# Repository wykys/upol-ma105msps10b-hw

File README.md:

# Multikanálový analyzátor 105 MSPS 10b

Vývoj hardware pro multikanálovou analýzu.

## Datasheets
Technická dokumentace používaná k vývoji.
### FPGA Xilinx 7 Series
- [Vivado Design Suite User Guide](https://www.xilinx.com/support/documentation/sw_manuals/xilinx2016_2/ug908-vivado-programming-debugging.pdf)
- [7 Series FPGAs Data Sheet: Overview](https://www.xilinx.com/support/documentation/data_sheets/ds180_7Series_Overview.pdf)
- [DC and AC Switching Characteristics](https://www.xilinx.com/support/documentation/data_sheets/ds189-spartan-7-data-sheet.pdf)
- [7 Series FPGAs Configuration User Guide](https://www.xilinx.com/support/documentation/user_guides/ug470_7Series_Config.pdf)
- [Using SPI Flash with 7 Series FPGAs](https://www.xilinx.com/support/documentation/application_notes/xapp586-spi-flash.pdf)
- [Spartan-7 FPGA Configuration with SPI Flash and Bank 14 at 1.35V](https://www.xilinx.com/support/documentation/application_notes/xapp1313-spartan-spi-config.pdf)
- [7 Series FPGAs SelectIO Resources User Guide](https://www.xilinx.com/support/documentation/user_guides/ug471_7Series_SelectIO.pdf)
- [7 Series FPGAs PCB Design Guide](https://www.xilinx.com/support/documentation/user_guides/ug483_7Series_PCB.pdf)
- [7 Series FPGAs Packaging and Pinout](https://www.xilinx.com/support/documentation/user_guides/ug475_7Series_Pkg_Pinout.pdf)

### Další dokumenty
- [Přehled logických obvodů ST](https://www.mouser.com/catalog/supplier/library/pdf/STLogic.pdf)
- [Zakončování LVCMOS](https://www.idt.com/eu/en/document/apn/953-quick-guide-output-terminations)
- [USB specifikace](https://www.silabs.com/documents/public/application-notes/AN0046.pdf)

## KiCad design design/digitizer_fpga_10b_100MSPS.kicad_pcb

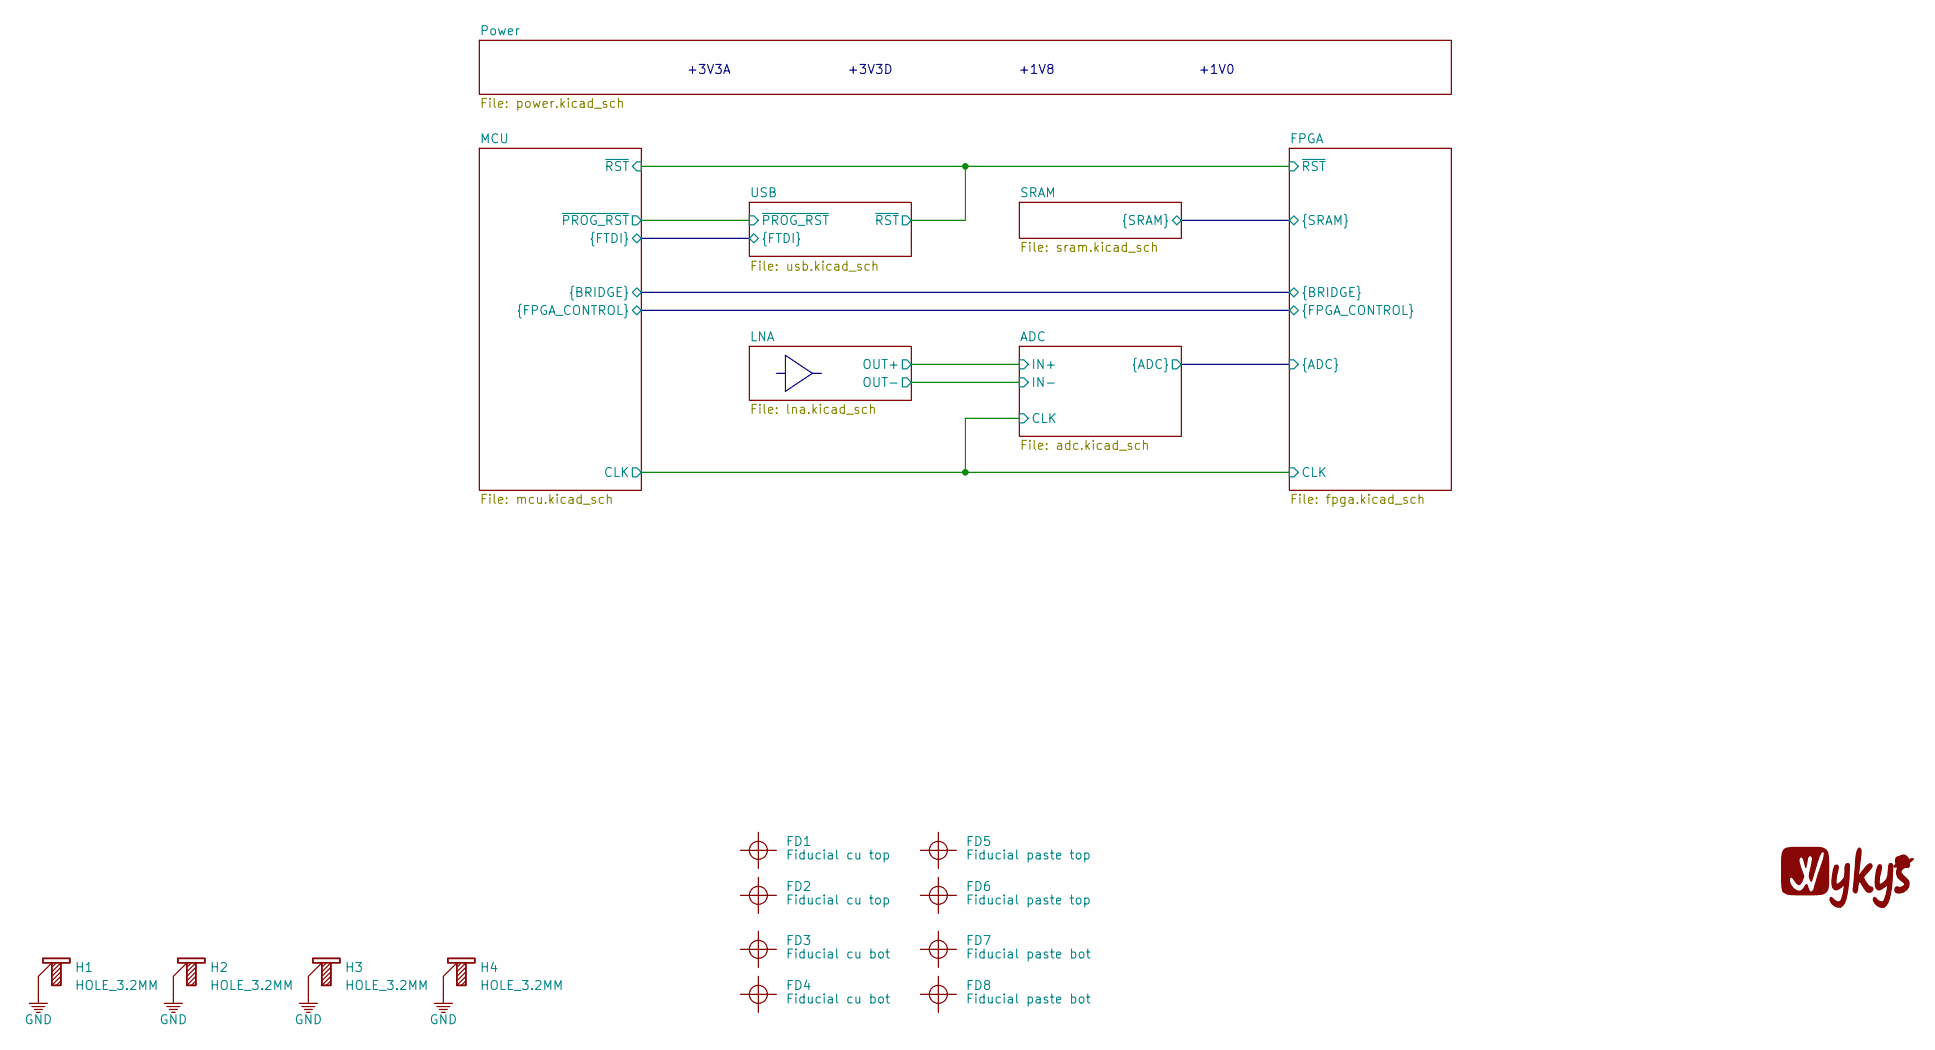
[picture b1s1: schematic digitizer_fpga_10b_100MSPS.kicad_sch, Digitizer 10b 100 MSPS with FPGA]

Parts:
FD1, FD2: Fiducial cu top; Fiducial_Pad_1.5mm_Outer_2.5mm
FD3, FD4: Fiducial cu bot; Fiducial_Pad_1.5mm_Outer_2.5mm
FD5, FD6: Fiducial paste top; Fiducial_Paste_Pad_1.5mm_Outer_2.5mm
FD7, FD8: Fiducial paste bot; Fiducial_Paste_Pad_1.5mm_Outer_2.5mm
GR1: Wykys; wykys_small_skill
H1, H2, H3, H4: HOLE_3.2MM; MountingHole_3.2mm_M3_Pad_Via

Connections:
GND: H1.1, H2.1, H3.1, H4.1; also elsewhere on the board

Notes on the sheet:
+3V3A
+3V3D
+1V8
+1V0

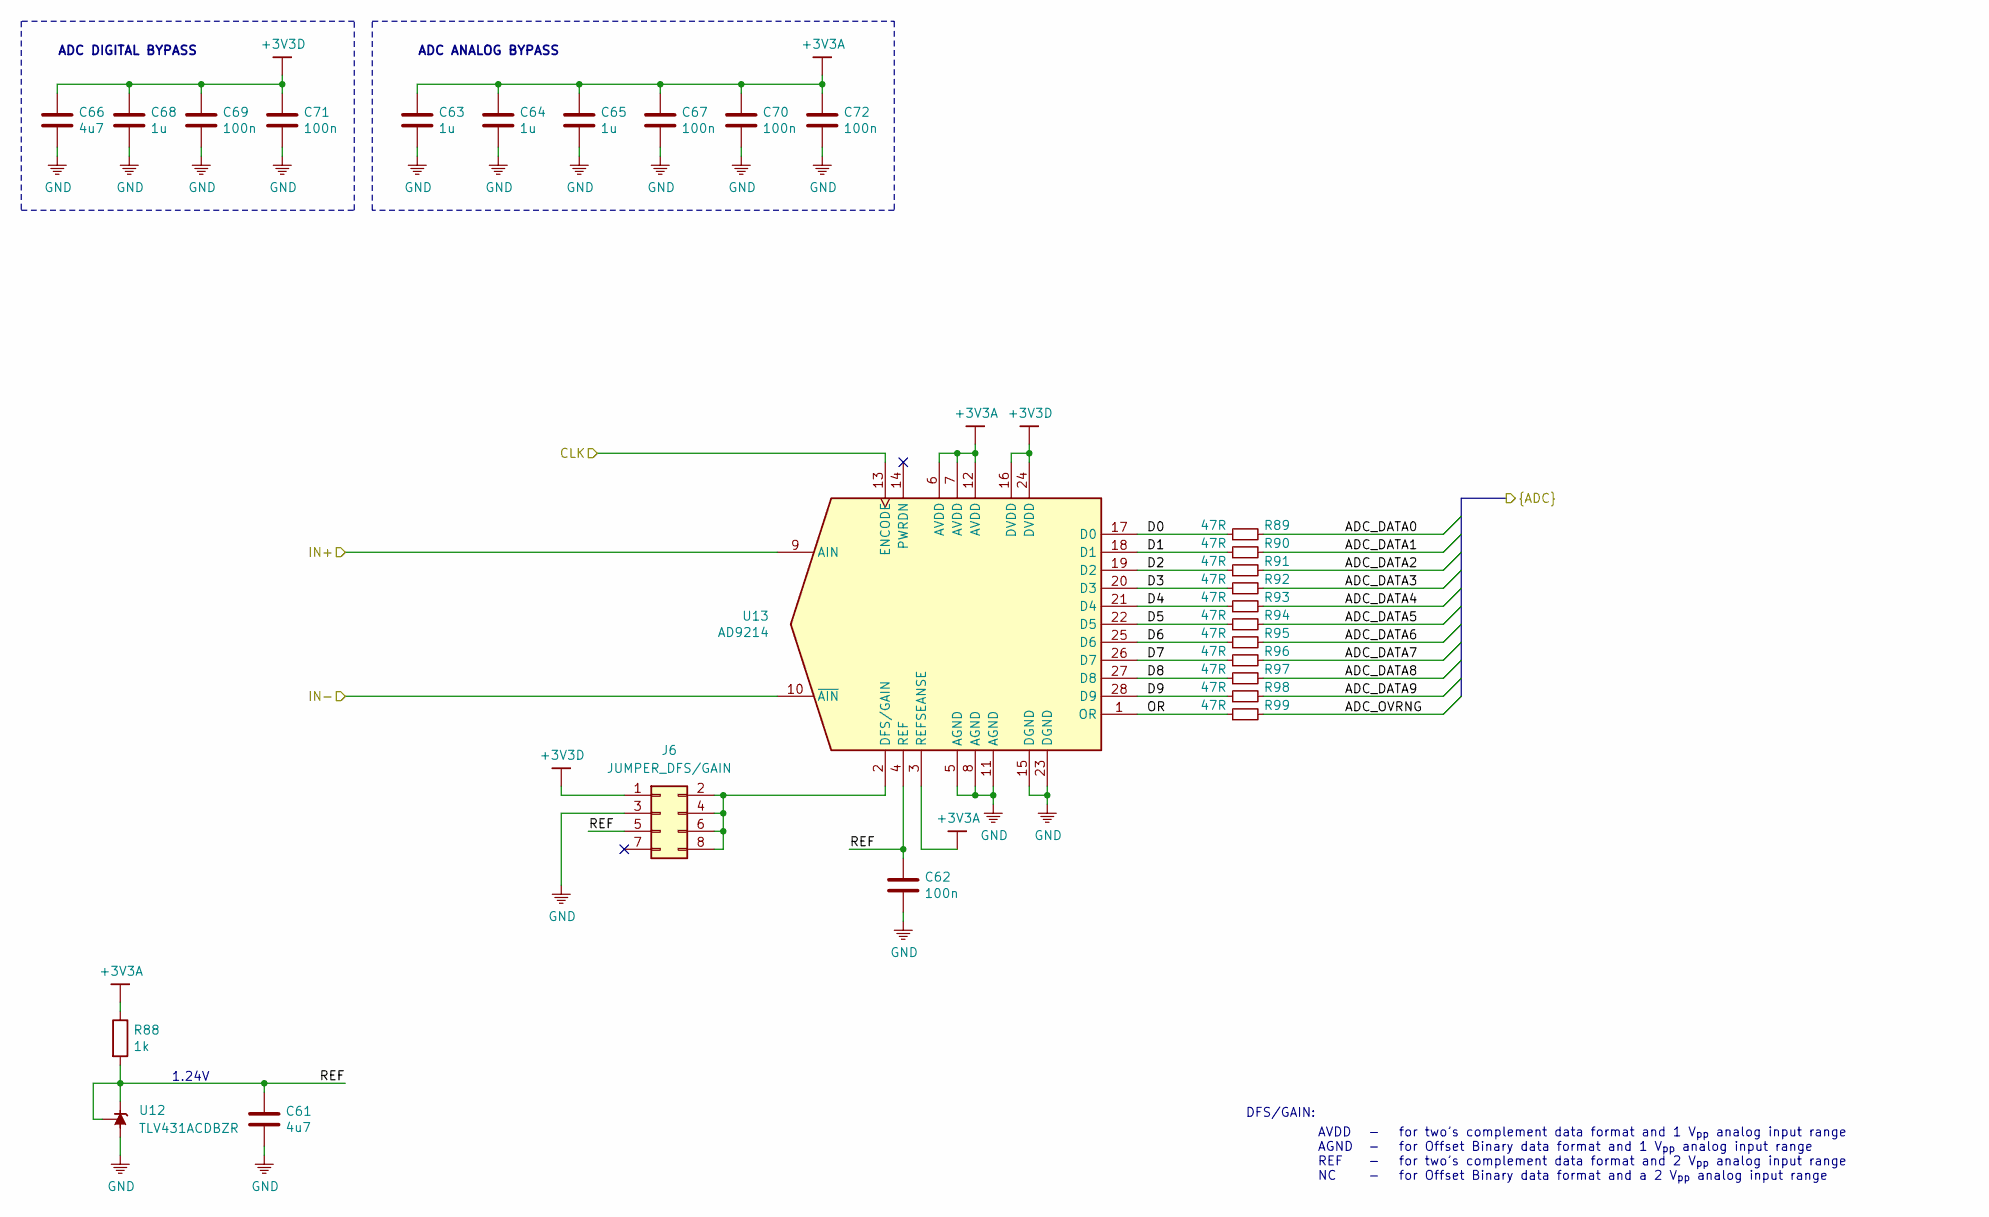
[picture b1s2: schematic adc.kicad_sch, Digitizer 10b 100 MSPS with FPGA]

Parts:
C61, C66: 4u7; C_0402_1005Metric
C62, C67, C69, C70, C71, C72: 100n; C_0402_1005Metric
C63, C64, C65, C68: 1u; C_0402_1005Metric
J6: JUMPER_DFS/GAIN; PinHeader_2x04_P2.54mm_Vertical
R88: 1k; R_0603_1608Metric
R89, R90, R91, R92, R93, R94, R95, R96, R97, R98, R99: 47R; R_0402_1005Metric
U12: TLV431ACDBZR; SOT-23
U13: AD9214; SSOP-28_5.3x10.2mm_P0.65mm

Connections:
+3V3A: C63.1, C64.1, C65.1, C67.1, C70.1, C72.1, R88.1, U13.3 (REFSEANSE), U13.6 (AVDD), U13.7 (AVDD), U13.12 (AVDD); also elsewhere on the board
+3V3D: C66.1, C68.1, C69.1, C71.1, J6.1, U13.16 (DVDD), U13.24 (DVDD); also elsewhere on the board
/ADC/ADC_DATA0: R89.2; also elsewhere on the board
/ADC/ADC_DATA1: R90.2; also elsewhere on the board
/ADC/ADC_DATA2: R91.2; also elsewhere on the board
/ADC/ADC_DATA3: R92.2; also elsewhere on the board
/ADC/ADC_DATA4: R93.2; also elsewhere on the board
/ADC/ADC_DATA5: R94.2; also elsewhere on the board
/ADC/ADC_DATA6: R95.2; also elsewhere on the board
/ADC/ADC_DATA7: R96.2; also elsewhere on the board
/ADC/ADC_DATA8: R97.2; also elsewhere on the board
/ADC/ADC_DATA9: R98.2; also elsewhere on the board
/ADC/ADC_OVRNG: R99.2; also elsewhere on the board
/ADC/CLK: U13.13 (ENCODE); also elsewhere on the board
/ADC/D0: R89.1, U13.17 (D0)
/ADC/D1: R90.1, U13.18 (D1)
/ADC/D2: R91.1, U13.19 (D2)
/ADC/D3: R92.1, U13.20 (D3)
/ADC/D4: R93.1, U13.21 (D4)
/ADC/D5: R94.1, U13.22 (D5)
/ADC/D6: R95.1, U13.25 (D6)
/ADC/D7: R96.1, U13.26 (D7)
/ADC/D8: R97.1, U13.27 (D8)
/ADC/D9: R98.1, U13.28 (D9)
/ADC/IN+: U13.9 (AIN); also elsewhere on the board
/ADC/IN-: U13.10 (~AIN); also elsewhere on the board
/ADC/OR: R99.1, U13.1 (OR)
/ADC/REF: C61.1, C62.1, J6.5, R88.2, U12.1 (K), U12.2 (REF), U13.4 (REF)
GND: C61.2, C62.2, C63.2, C64.2, C65.2, C66.2, C67.2, C68.2, C69.2, C70.2, C71.2, C72.2, J6.3, U12.3 (A), U13.5 (AGND), U13.8 (AGND), U13.11 (AGND), U13.15 (DGND), U13.23 (DGND); also elsewhere on the board
unnamed: J6.2, J6.4, J6.6, J6.8, U13.2 (DFS/GAIN)

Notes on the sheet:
ADC DIGITAL BYPASS
1.24V
ADC ANALOG BYPASS
DFS/GAIN:
AVDD AGND REF NC
- - - -
for two’s complement data format and 1 V_{pp} analog input range for Offset Binary data format and 1 V_{pp} analog input range for two’s complement data format and 2 V_{pp} analog input range for Offset Binary data format and a 2 V_{pp} analog input range

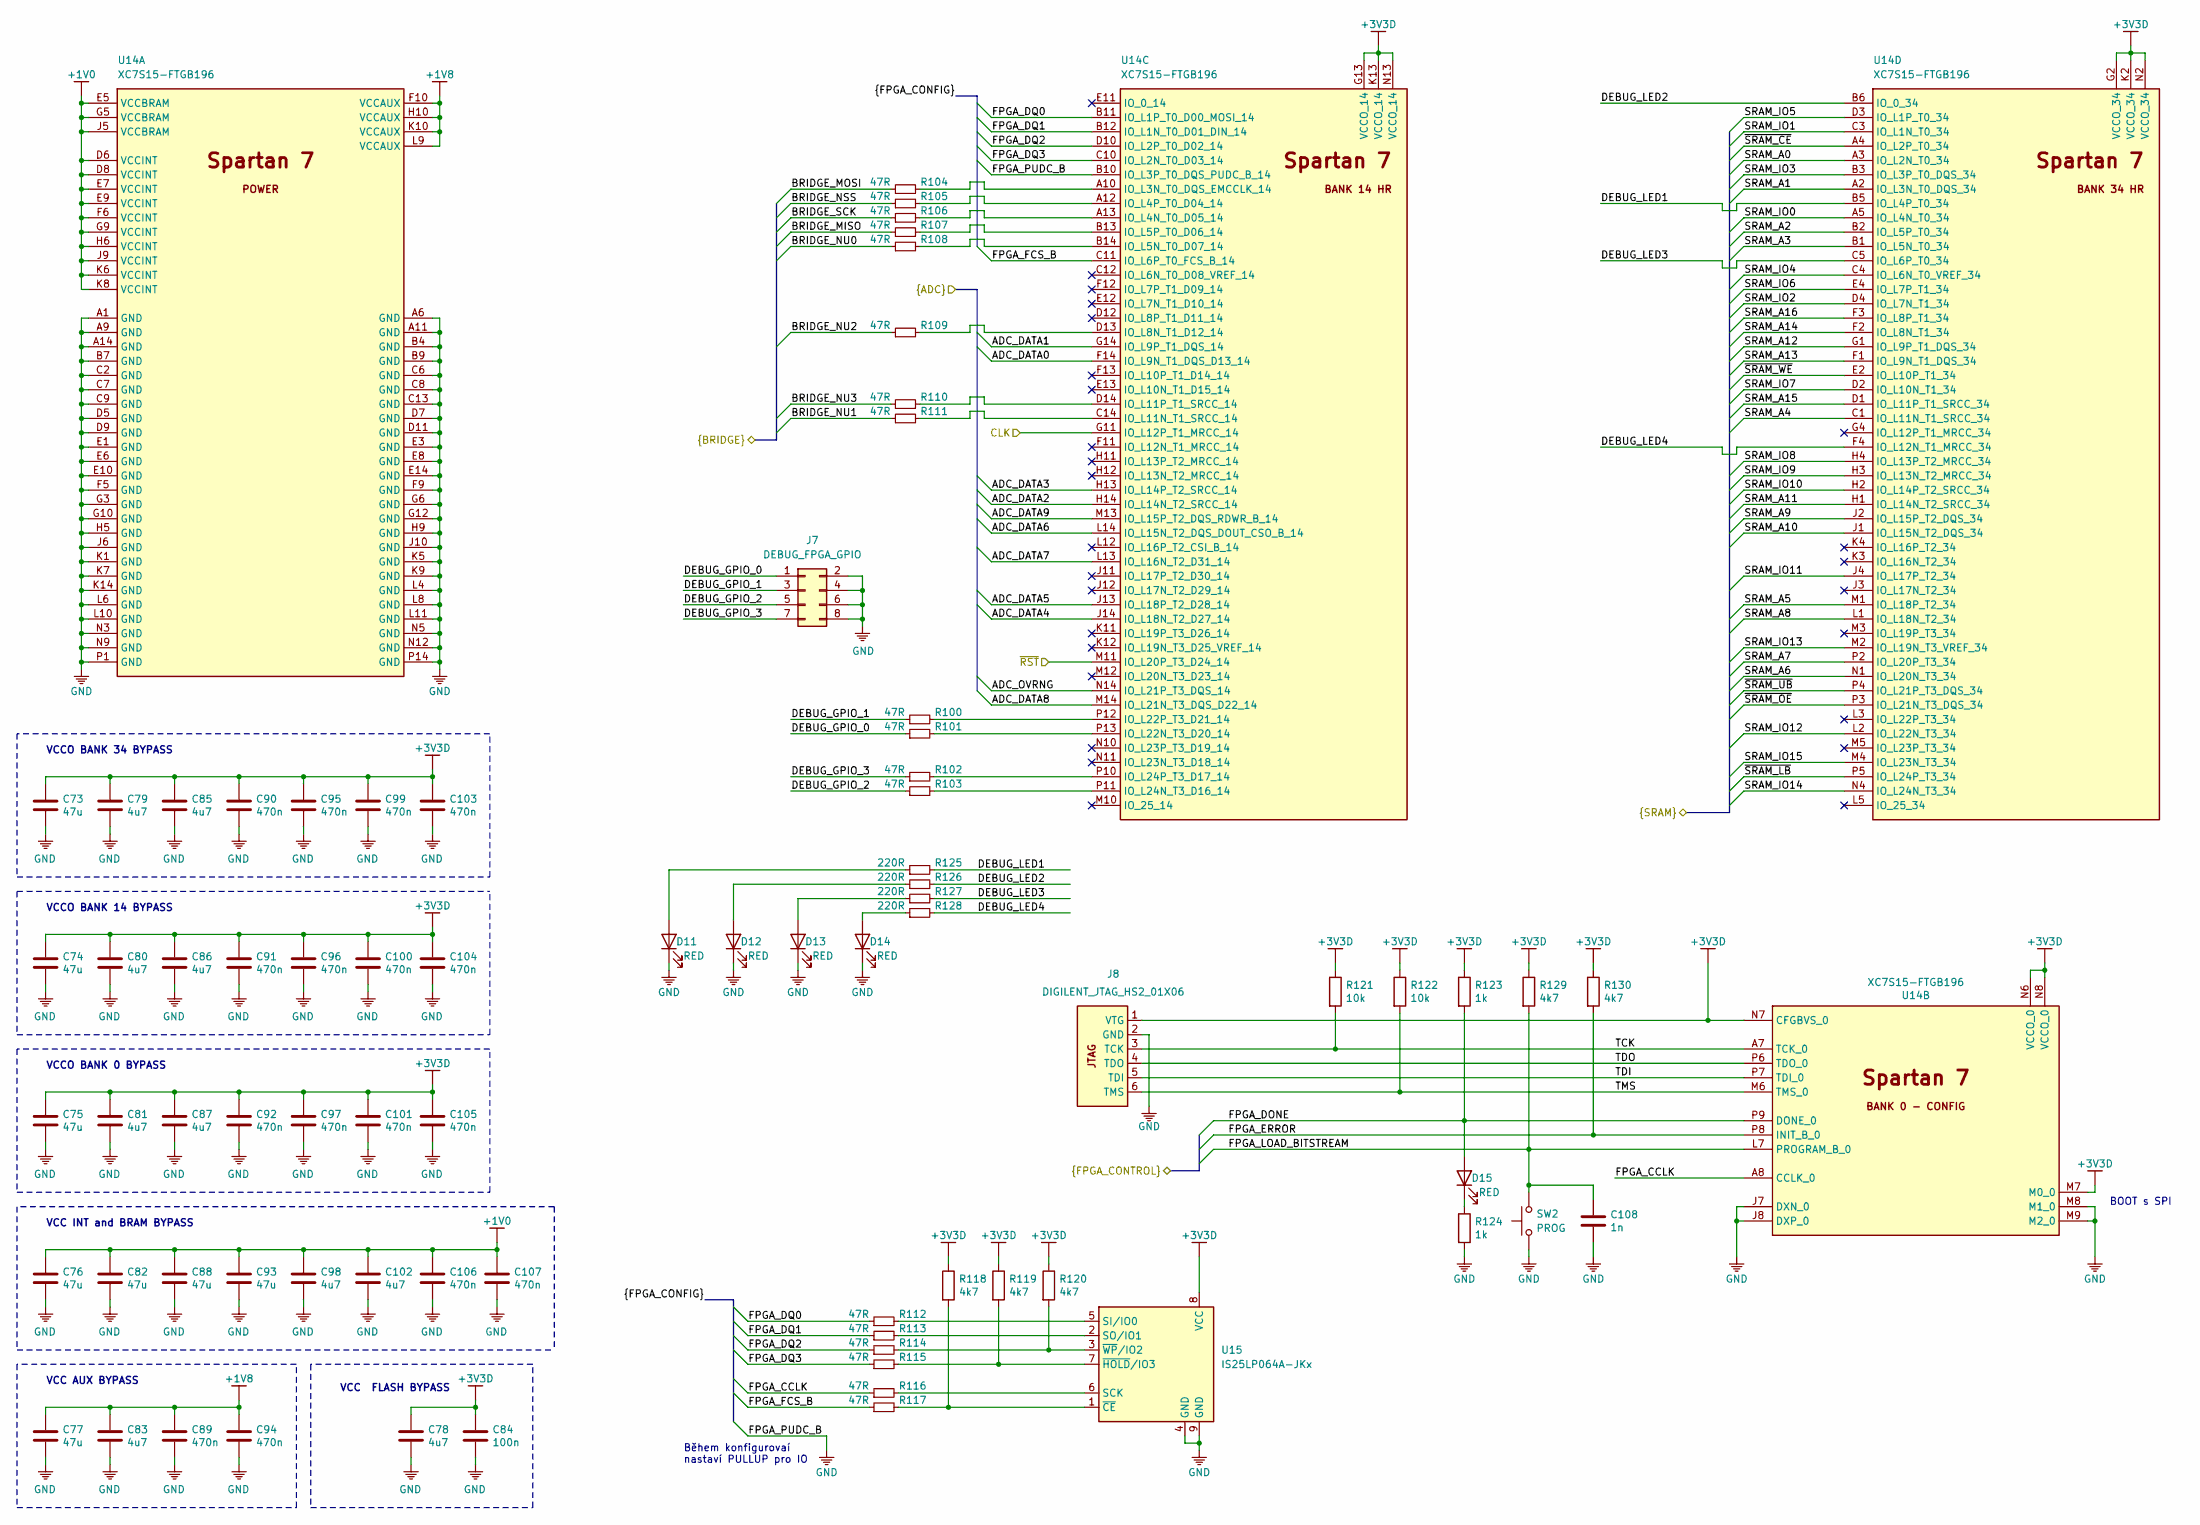
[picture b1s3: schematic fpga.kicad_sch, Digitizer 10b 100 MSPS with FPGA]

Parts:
C73, C74, C75, C76, C77, C82, C88, C93: 47u; C_0402_1005Metric
C78, C79, C80, C81, C83, C85, C86, C87, C98, C102: 4u7; C_0402_1005Metric
C84: 100n; C_0402_1005Metric
C89, C90, C91, C92, C94, C95, C96, C97, C99, C100, C101, C103, C104, C105, C106, C107: 470n; C_0402_1005Metric
C108: 1n; C_0402_1005Metric
D11, D12, D13, D14, D15: RED; LED_0805_2012Metric
J7: DEBUG_FPGA_GPIO; PinHeader_2x04_P2.54mm_Vertical
J8: DIGILENT_JTAG_HS2_01X06; PinHeader_1x06_P2.54mm_Vertical
R100, R101, R102, R103, R104, R105, R106, R107, R108, R109, R110, R111, R112, R113, R114, R115, R116, R117: 47R; R_0402_1005Metric
R118, R119, R120, R129, R130: 4k7; R_0603_1608Metric
R121, R122: 10k; R_0603_1608Metric
R123, R124: 1k; R_0603_1608Metric
R125, R126, R127, R128: 220R; R_0603_1608Metric
SW2: PROG; SW_SPST_CK_RS282G05A3
U14: XC7S15-FTGB196; Xilinx_FTGB196
U15: IS25LP064A-JKx; WSON-8-1EP_6x5mm_P1.27mm_EP3.4x4mm

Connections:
+1V0: C76.1, C82.1, C88.1, C93.1, C98.1, C102.1, C106.1, C107.1, U14.D6 (VCCINT), U14.D8 (VCCINT), U14.E5 (VCCBRAM), U14.E7 (VCCINT), U14.E9 (VCCINT), U14.F6 (VCCINT), U14.G5 (VCCBRAM), U14.G9 (VCCINT), U14.H6 (VCCINT), U14.J5 (VCCBRAM), U14.J9 (VCCINT), U14.K6 (VCCINT), U14.K8 (VCCINT); also elsewhere on the board
+1V8: C77.1, C83.1, C89.1, C94.1, U14.F10 (VCCAUX), U14.H10 (VCCAUX), U14.K10 (VCCAUX), U14.L9 (VCCAUX); also elsewhere on the board
+3V3D: C73.1, C74.1, C75.1, C78.1, C79.1, C80.1, C81.1, C84.1, C85.1, C86.1, C87.1, C90.1, C91.1, C92.1, C95.1, C96.1, C97.1, C99.1, C100.1, C101.1, C103.1, C104.1, C105.1, J8.1 (VTG), R118.1, R119.1, R120.1, R121.1, R122.1, R123.1, R129.1, R130.1, U14.G2 (VCCO_34), U14.G13 (VCCO_14), U14.K2 (VCCO_34), U14.K13 (VCCO_14), U14.M7 (M0_0), U14.N2 (VCCO_34), U14.N6 (VCCO_0), U14.N7 (CFGBVS_0), U14.N8 (VCCO_0), U14.N13 (VCCO_14), U15.8 (VCC); also elsewhere on the board
/ADC/ADC_DATA0: U14.F14 (IO_L9N_T1_DQS_D13_14); also elsewhere on the board
/ADC/ADC_DATA1: U14.G14 (IO_L9P_T1_DQS_14); also elsewhere on the board
/ADC/ADC_DATA2: U14.H14 (IO_L14N_T2_SRCC_14); also elsewhere on the board
/ADC/ADC_DATA3: U14.H13 (IO_L14P_T2_SRCC_14); also elsewhere on the board
/ADC/ADC_DATA4: U14.J14 (IO_L18N_T2_D27_14); also elsewhere on the board
/ADC/ADC_DATA5: U14.J13 (IO_L18P_T2_D28_14); also elsewhere on the board
/ADC/ADC_DATA6: U14.L14 (IO_L15N_T2_DQS_DOUT_CSO_B_14); also elsewhere on the board
/ADC/ADC_DATA7: U14.L13 (IO_L16N_T2_D31_14); also elsewhere on the board
/ADC/ADC_DATA8: U14.M14 (IO_L21N_T3_DQS_D22_14); also elsewhere on the board
/ADC/ADC_DATA9: U14.M13 (IO_L15P_T2_DQS_RDWR_B_14); also elsewhere on the board
/ADC/ADC_OVRNG: U14.N14 (IO_L21P_T3_DQS_14); also elsewhere on the board
/ADC/CLK: U14.G11 (IO_L12P_T1_MRCC_14); also elsewhere on the board
/FPGA/BRIDGE_MISO: R107.1; also elsewhere on the board
/FPGA/BRIDGE_MOSI: R104.1; also elsewhere on the board
/FPGA/BRIDGE_NSS: R105.1; also elsewhere on the board
/FPGA/BRIDGE_NU0: R108.1; also elsewhere on the board
/FPGA/BRIDGE_NU1: R111.1; also elsewhere on the board
/FPGA/BRIDGE_NU2: R109.1; also elsewhere on the board
/FPGA/BRIDGE_NU3: R110.1; also elsewhere on the board
/FPGA/BRIDGE_SCK: R106.1; also elsewhere on the board
/FPGA/DEBUG_GPIO_0: J7.1, R101.1
/FPGA/DEBUG_GPIO_1: J7.3, R100.1
/FPGA/DEBUG_GPIO_2: J7.5, R103.1
/FPGA/DEBUG_GPIO_3: J7.7, R102.1
/FPGA/DEBUG_LED1: R125.2, U14.B5 (IO_L4P_T0_34)
/FPGA/DEBUG_LED2: R126.2, U14.B6 (IO_0_34)
/FPGA/DEBUG_LED3: R127.2, U14.C5 (IO_L6P_T0_34)
/FPGA/DEBUG_LED4: R128.2, U14.F4 (IO_L12N_T1_MRCC_34)
/FPGA/FPGA_CCLK: R116.1, U14.A8 (CCLK_0)
/FPGA/FPGA_DONE: D15.2 (A), R123.2, U14.P9 (DONE_0); also elsewhere on the board
/FPGA/FPGA_DQ0: R112.1, U14.B11 (IO_L1P_T0_D00_MOSI_14)
/FPGA/FPGA_DQ1: R113.1, U14.B12 (IO_L1N_T0_D01_DIN_14)
/FPGA/FPGA_DQ2: R114.1, U14.D10 (IO_L2P_T0_D02_14)
/FPGA/FPGA_DQ3: R115.1, U14.C10 (IO_L2N_T0_D03_14)
/FPGA/FPGA_ERROR: R130.2, U14.P8 (INIT_B_0); also elsewhere on the board
/FPGA/FPGA_FCS_B: R117.1, U14.C11 (IO_L6P_T0_FCS_B_14)
/FPGA/FPGA_LOAD_BITSTREAM: C108.1, R129.2, SW2.2, U14.L7 (PROGRAM_B_0); also elsewhere on the board
/FPGA/SRAM_A0: U14.A3 (IO_L2N_T0_34); also elsewhere on the board
/FPGA/SRAM_A1: U14.A2 (IO_L3N_T0_DQS_34); also elsewhere on the board
/FPGA/SRAM_A2: U14.B2 (IO_L5P_T0_34); also elsewhere on the board
/FPGA/SRAM_A3: U14.B1 (IO_L5N_T0_34); also elsewhere on the board
/FPGA/SRAM_A4: U14.C1 (IO_L11N_T1_SRCC_34); also elsewhere on the board
/FPGA/SRAM_A5: U14.M1 (IO_L18P_T2_34); also elsewhere on the board
/FPGA/SRAM_A6: U14.N1 (IO_L20N_T3_34); also elsewhere on the board
/FPGA/SRAM_A7: U14.P2 (IO_L20P_T3_34); also elsewhere on the board
/FPGA/SRAM_A8: U14.L1 (IO_L18N_T2_34); also elsewhere on the board
/FPGA/SRAM_A9: U14.J2 (IO_L15P_T2_DQS_34); also elsewhere on the board
/FPGA/SRAM_A10: U14.J1 (IO_L15N_T2_DQS_34); also elsewhere on the board
/FPGA/SRAM_A11: U14.H1 (IO_L14N_T2_SRCC_34); also elsewhere on the board
/FPGA/SRAM_A12: U14.G1 (IO_L9P_T1_DQS_34); also elsewhere on the board
/FPGA/SRAM_A13: U14.F1 (IO_L9N_T1_DQS_34); also elsewhere on the board
/FPGA/SRAM_A14: U14.F2 (IO_L8N_T1_34); also elsewhere on the board
/FPGA/SRAM_A15: U14.D1 (IO_L11P_T1_SRCC_34); also elsewhere on the board
/FPGA/SRAM_A16: U14.F3 (IO_L8P_T1_34); also elsewhere on the board
/FPGA/SRAM_IO0: U14.A5 (IO_L4N_T0_34); also elsewhere on the board
/FPGA/SRAM_IO1: U14.C3 (IO_L1N_T0_34); also elsewhere on the board
/FPGA/SRAM_IO2: U14.D4 (IO_L7N_T1_34); also elsewhere on the board
/FPGA/SRAM_IO3: U14.B3 (IO_L3P_T0_DQS_34); also elsewhere on the board
/FPGA/SRAM_IO4: U14.C4 (IO_L6N_T0_VREF_34); also elsewhere on the board
/FPGA/SRAM_IO5: U14.D3 (IO_L1P_T0_34); also elsewhere on the board
/FPGA/SRAM_IO6: U14.E4 (IO_L7P_T1_34); also elsewhere on the board
/FPGA/SRAM_IO7: U14.D2 (IO_L10N_T1_34); also elsewhere on the board
/FPGA/SRAM_IO8: U14.H4 (IO_L13P_T2_MRCC_34); also elsewhere on the board
/FPGA/SRAM_IO9: U14.H3 (IO_L13N_T2_MRCC_34); also elsewhere on the board
/FPGA/SRAM_IO10: U14.H2 (IO_L14P_T2_SRCC_34); also elsewhere on the board
/FPGA/SRAM_IO11: U14.J4 (IO_L17P_T2_34); also elsewhere on the board
/FPGA/SRAM_IO12: U14.L2 (IO_L22N_T3_34); also elsewhere on the board
/FPGA/SRAM_IO13: U14.M2 (IO_L19N_T3_VREF_34); also elsewhere on the board
/FPGA/SRAM_IO14: U14.N4 (IO_L24N_T3_34); also elsewhere on the board
/FPGA/SRAM_IO15: U14.M4 (IO_L23N_T3_34); also elsewhere on the board
/FPGA/TCK: J8.3 (TCK), R121.2, U14.A7 (TCK_0)
/FPGA/TDI: J8.5 (TDI), U14.P7 (TDI_0)
/FPGA/TDO: J8.4 (TDO), U14.P6 (TDO_0)
/FPGA/TMS: J8.6 (TMS), R122.2, U14.M6 (TMS_0)
/FPGA/~RST: U14.M11 (IO_L20P_T3_D24_14); also elsewhere on the board
/FPGA/~SRAM_CE: U14.A4 (IO_L2P_T0_34); also elsewhere on the board
/FPGA/~SRAM_LB: U14.P5 (IO_L24P_T3_34); also elsewhere on the board
/FPGA/~SRAM_OE: U14.P3 (IO_L21N_T3_DQS_34); also elsewhere on the board
/FPGA/~SRAM_UB: U14.P4 (IO_L21P_T3_DQS_34); also elsewhere on the board
/FPGA/~SRAM_WE: U14.E2 (IO_L10P_T1_34); also elsewhere on the board
GND: C73.2, C74.2, C75.2, C76.2, C77.2, C78.2, C79.2, C80.2, C81.2, C82.2, C83.2, C84.2, C85.2, C86.2, C87.2, C88.2, C89.2, C90.2, C91.2, C92.2, C93.2, C94.2, C95.2, C96.2, C97.2, C98.2, C99.2, C100.2, C101.2, C102.2, C103.2, C104.2, C105.2, C106.2, C107.2, C108.2, D11.1 (K), D12.1 (K), D13.1 (K), D14.1 (K), J7.2, J7.4, J7.6, J7.8, J8.2 (GND), R124.2, SW2.1, U14.A1 (GND), U14.A6 (GND), U14.A9 (GND), U14.A11 (GND), U14.A14 (GND), U14.B4 (GND), U14.B7 (GND), U14.B9 (GND), U14.B10 (IO_L3P_T0_DQS_PUDC_B_14), U14.C2 (GND), U14.C6 (GND), U14.C7 (GND), U14.C8 (GND), U14.C9 (GND), U14.C13 (GND), U14.D5 (GND), U14.D7 (GND), U14.D9 (GND), U14.D11 (GND), U14.E1 (GND), U14.E3 (GND), U14.E6 (GND), U14.E8 (GND), U14.E10 (GND), U14.E14 (GND), U14.F5 (GND), U14.F9 (GND), U14.G3 (GND), U14.G6 (GND), U14.G10 (GND), U14.G12 (GND), U14.H5 (GND), U14.H9 (GND), U14.J6 (GND), U14.J7 (DXN_0), U14.J8 (DXP_0), U14.J10 (GND), U14.K1 (GND), U14.K5 (GND), U14.K7 (GND), U14.K9 (GND), U14.K14 (GND), U14.L4 (GND), U14.L6 (GND), U14.L8 (GND), U14.L10 (GND), U14.L11 (GND), U14.M8 (M1_0), U14.M9 (M2_0), U14.N3 (GND), U14.N5 (GND), U14.N9 (GND), U14.N12 (GND), U14.P1 (GND), U14.P14 (GND), U15.4 (GND), U15.9 (GND); also elsewhere on the board
unnamed: D11.2 (A), R125.1
unnamed: D12.2 (A), R126.1
unnamed: D13.2 (A), R127.1
unnamed: D14.2 (A), R128.1
unnamed: D15.1 (K), R124.1
unnamed: R100.2, U14.P12 (IO_L22P_T3_D21_14)
unnamed: R101.2, U14.P13 (IO_L22N_T3_D20_14)
unnamed: R102.2, U14.P10 (IO_L24P_T3_D17_14)
unnamed: R103.2, U14.P11 (IO_L24N_T3_D16_14)
unnamed: R104.2, U14.A10 (IO_L3N_T0_DQS_EMCCLK_14)
unnamed: R105.2, U14.A12 (IO_L4P_T0_D04_14)
unnamed: R106.2, U14.A13 (IO_L4N_T0_D05_14)
unnamed: R107.2, U14.B13 (IO_L5P_T0_D06_14)
unnamed: R108.2, U14.B14 (IO_L5N_T0_D07_14)
unnamed: R109.2, U14.D13 (IO_L8N_T1_D12_14)
unnamed: R110.2, U14.D14 (IO_L11P_T1_SRCC_14)
unnamed: R111.2, U14.C14 (IO_L11N_T1_SRCC_14)
unnamed: R112.2, U15.5 (SI/IO0)
unnamed: R113.2, U15.2 (SO/IO1)
unnamed: R114.2, R120.2, U15.3 (~WP~/IO2)
unnamed: R115.2, R119.2, U15.7 (~HOLD~/IO3)
unnamed: R116.2, U15.6 (SCK)
unnamed: R117.2, R118.2, U15.1 (~CE)

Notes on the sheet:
VCCO BANK 34 BYPASS
VCCO BANK 14 BYPASS
VCCO BANK 0 BYPASS
VCC INT and BRAM BYPASS
VCC AUX BYPASS
VCC FLASH BYPASS
Během konfigurovaí nastaví PULLUP pro IO
BOOT s SPI

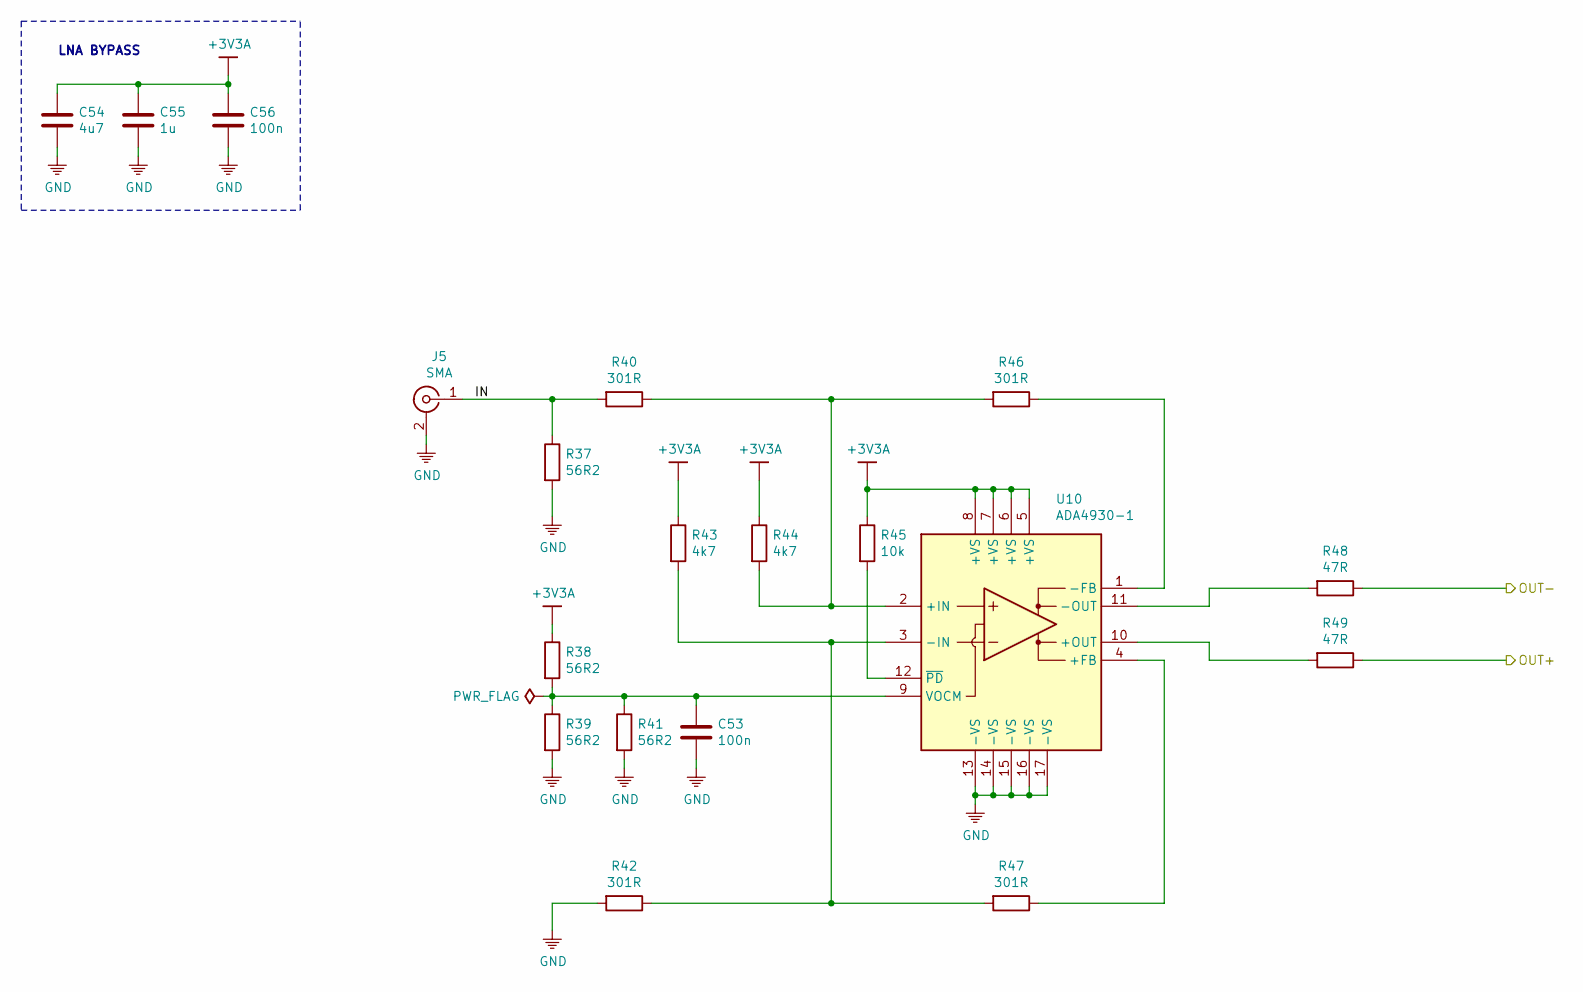
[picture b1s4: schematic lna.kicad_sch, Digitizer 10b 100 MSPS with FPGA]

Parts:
C53, C56: 100n; C_0402_1005Metric
C54: 4u7; C_0402_1005Metric
C55: 1u; C_0402_1005Metric
J5: SMA; SMA_Samtec_SMA-J-P-X-ST-EM1_EdgeMount
R37, R38, R39, R41: 56R2; R_0603_1608Metric
R40, R42, R46, R47: 301R; R_0603_1608Metric
R43, R44: 4k7; R_0603_1608Metric
R45: 10k; R_0603_1608Metric
R48, R49: 47R; R_0402_1005Metric
U10: ADA4930-1; LFCSP-16-1EP_3x3mm_P0.5mm_EP1.7x1.7mm

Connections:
+3V3A: C54.1, C55.1, C56.1, R38.1, R43.1, R44.1, R45.1, U10.5 (+VS), U10.6 (+VS), U10.7 (+VS), U10.8 (+VS); also elsewhere on the board
/ADC/IN+: R49.1; also elsewhere on the board
/ADC/IN-: R48.1; also elsewhere on the board
/LNA/IN: J5.1 (In), R37.1, R40.2
GND: C53.2, C54.2, C55.2, C56.2, J5.2 (Ext), R37.2, R39.2, R41.2, R42.2, U10.13 (-VS), U10.14 (-VS), U10.15 (-VS), U10.16 (-VS), U10.17 (-VS); also elsewhere on the board
unnamed: C53.1, R38.2, R39.1, R41.1, U10.9 (VOCM)
unnamed: R40.1, R44.2, R46.2, U10.2 (+IN)
unnamed: R42.1, R43.2, R47.2, U10.3 (-IN)
unnamed: R45.2, U10.12 (~PD)
unnamed: R46.1, U10.1 (-FB)
unnamed: R47.1, U10.4 (+FB)
unnamed: R48.2, U10.11 (-OUT)
unnamed: R49.2, U10.10 (+OUT)

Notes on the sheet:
LNA BYPASS

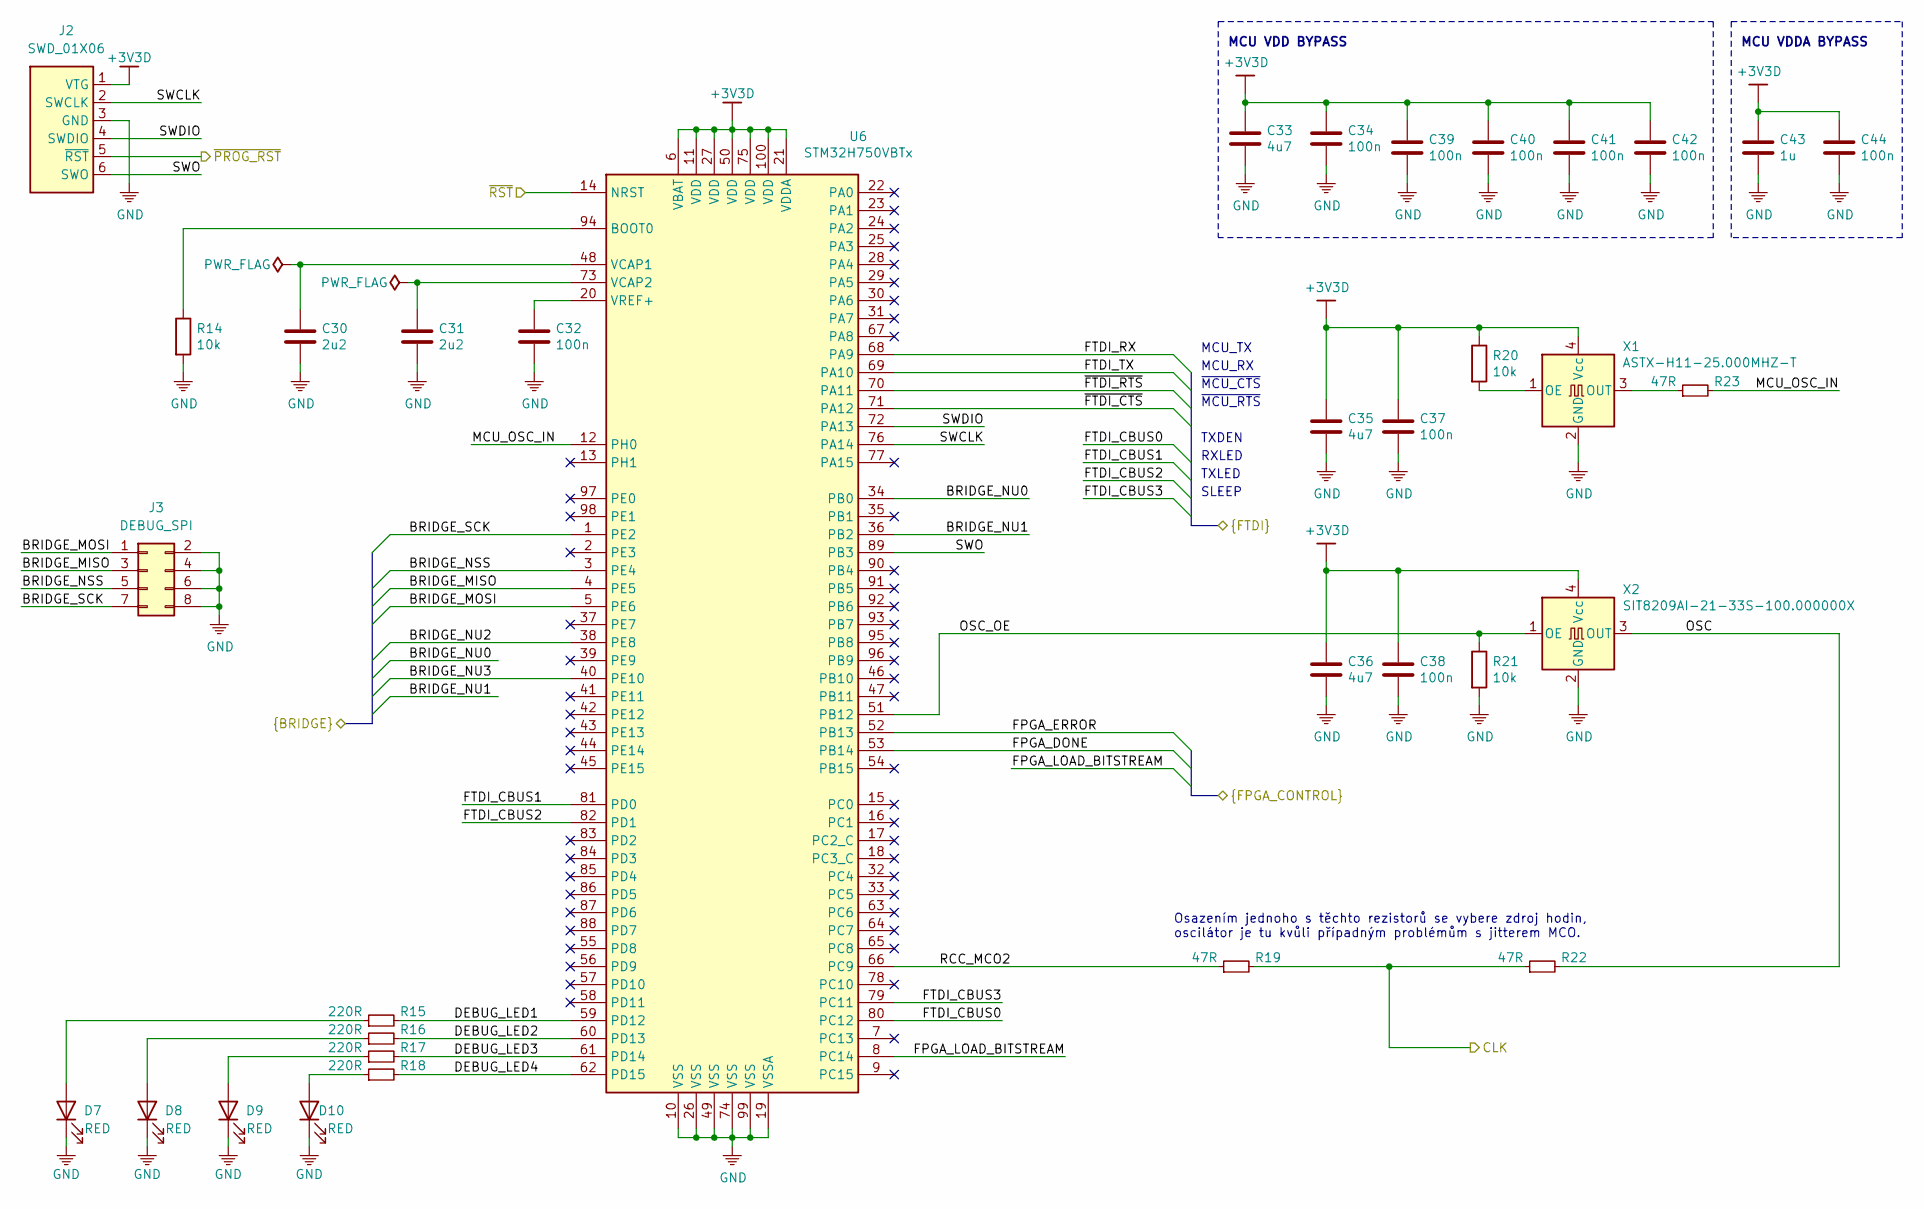
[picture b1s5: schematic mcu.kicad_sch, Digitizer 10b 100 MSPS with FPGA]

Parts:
C30, C31: 2u2; C_0402_1005Metric
C32, C34, C37, C38, C39, C40, C41, C42, C44: 100n; C_0402_1005Metric
C33, C35, C36: 4u7; C_0402_1005Metric
C43: 1u; C_0402_1005Metric
D7, D8, D9, D10: RED; LED_0805_2012Metric
J2: SWD_01X06; PinHeader_1x06_P2.54mm_Vertical
J3: DEBUG_SPI; PinHeader_2x04_P2.54mm_Vertical
R14, R20, R21: 10k; R_0603_1608Metric
R15, R16, R17, R18: 220R; R_0603_1608Metric
R19, R22, R23: 47R; R_0402_1005Metric
U6: STM32H750VBTx; LQFP-100_14x14mm_P0.5mm
X1: ASTX-H11-25.000MHZ-T; Oscillator_SMD_SeikoEpson_SG8002CE-4Pin_3.2x2.5mm
X2: SIT8209AI-21-33S-100.000000X; Oscillator_SMD_SeikoEpson_SG8002CE-4Pin_3.2x2.5mm

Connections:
+3V3D: C33.1, C34.1, C35.1, C36.1, C37.1, C38.1, C39.1, C40.1, C41.1, C42.1, C43.1, C44.1, J2.1 (VTG), R20.1, U6.6 (VBAT), U6.11 (VDD), U6.21 (VDDA), U6.27 (VDD), U6.50 (VDD), U6.75 (VDD), U6.100 (VDD), X1.4 (Vcc), X2.4 (Vcc); also elsewhere on the board
/ADC/CLK: R19.2, R22.1; also elsewhere on the board
/FPGA/BRIDGE_MISO: J3.3, U6.4 (PE5); also elsewhere on the board
/FPGA/BRIDGE_MOSI: J3.1, U6.5 (PE6); also elsewhere on the board
/FPGA/BRIDGE_NSS: J3.5, U6.3 (PE4); also elsewhere on the board
/FPGA/BRIDGE_NU0: U6.34 (PB0); also elsewhere on the board
/FPGA/BRIDGE_NU1: U6.36 (PB2); also elsewhere on the board
/FPGA/BRIDGE_NU2: U6.38 (PE8); also elsewhere on the board
/FPGA/BRIDGE_NU3: U6.40 (PE10); also elsewhere on the board
/FPGA/BRIDGE_SCK: J3.7, U6.1 (PE2); also elsewhere on the board
/FPGA/FPGA_DONE: U6.53 (PB14); also elsewhere on the board
/FPGA/FPGA_ERROR: U6.52 (PB13); also elsewhere on the board
/FPGA/FPGA_LOAD_BITSTREAM: U6.8 (PC14); also elsewhere on the board
/FPGA/~RST: U6.14 (NRST); also elsewhere on the board
/MCU/DEBUG_LED1: R15.2, U6.59 (PD12)
/MCU/DEBUG_LED2: R16.2, U6.60 (PD13)
/MCU/DEBUG_LED3: R17.2, U6.61 (PD14)
/MCU/DEBUG_LED4: R18.2, U6.62 (PD15)
/MCU/FTDI_CBUS0: U6.80 (PC12); also elsewhere on the board
/MCU/FTDI_CBUS1: U6.81 (PD0); also elsewhere on the board
/MCU/FTDI_CBUS2: U6.82 (PD1); also elsewhere on the board
/MCU/FTDI_CBUS3: U6.79 (PC11); also elsewhere on the board
/MCU/FTDI_RX: U6.68 (PA9); also elsewhere on the board
/MCU/FTDI_TX: U6.69 (PA10); also elsewhere on the board
/MCU/MCU_OSC_IN: R23.2, U6.12 (PH0)
/MCU/OSC: R22.2, X2.3 (OUT)
/MCU/OSC_OE: R21.1, U6.51 (PB12), X2.1 (OE)
/MCU/RCC_MCO2: R19.1, U6.66 (PC9)
/MCU/SWCLK: J2.2 (SWCLK), U6.76 (PA14)
/MCU/SWDIO: J2.4 (SWDIO), U6.72 (PA13)
/MCU/SWO: J2.6 (SWO), U6.89 (PB3)
/MCU/~FTDI_CTS: U6.71 (PA12); also elsewhere on the board
/MCU/~FTDI_RTS: U6.70 (PA11); also elsewhere on the board
/MCU/~PROG_RST: J2.5 (~RST); also elsewhere on the board
GND: C30.2, C31.2, C32.2, C33.2, C34.2, C35.2, C36.2, C37.2, C38.2, C39.2, C40.2, C41.2, C42.2, C43.2, C44.2, D7.1 (K), D8.1 (K), D9.1 (K), D10.1 (K), J2.3 (GND), J3.2, J3.4, J3.6, J3.8, R14.2, R21.2, U6.10 (VSS), U6.19 (VSSA), U6.26 (VSS), U6.49 (VSS), U6.74 (VSS), U6.99 (VSS), X1.2 (GND), X2.2 (GND); also elsewhere on the board
unnamed: C30.1, U6.48 (VCAP1)
unnamed: C31.1, U6.73 (VCAP2)
unnamed: C32.1, U6.20 (VREF+)
unnamed: D7.2 (A), R15.1
unnamed: D8.2 (A), R16.1
unnamed: D9.2 (A), R17.1
unnamed: D10.2 (A), R18.1
unnamed: R14.1, U6.94 (BOOT0)
unnamed: R20.2, X1.1 (OE)
unnamed: R23.1, X1.3 (OUT)

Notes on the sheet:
Osazením jednoho s těchto rezistorů se vybere zdroj hodin, oscilátor je tu kvůli případným problémům s jitterem MCO.
MCU_TX
MCU_RX
~MCU_CTS
~MCU_RTS
TXDEN
RXLED
TXLED
SLEEP
MCU VDD BYPASS
MCU VDDA BYPASS
